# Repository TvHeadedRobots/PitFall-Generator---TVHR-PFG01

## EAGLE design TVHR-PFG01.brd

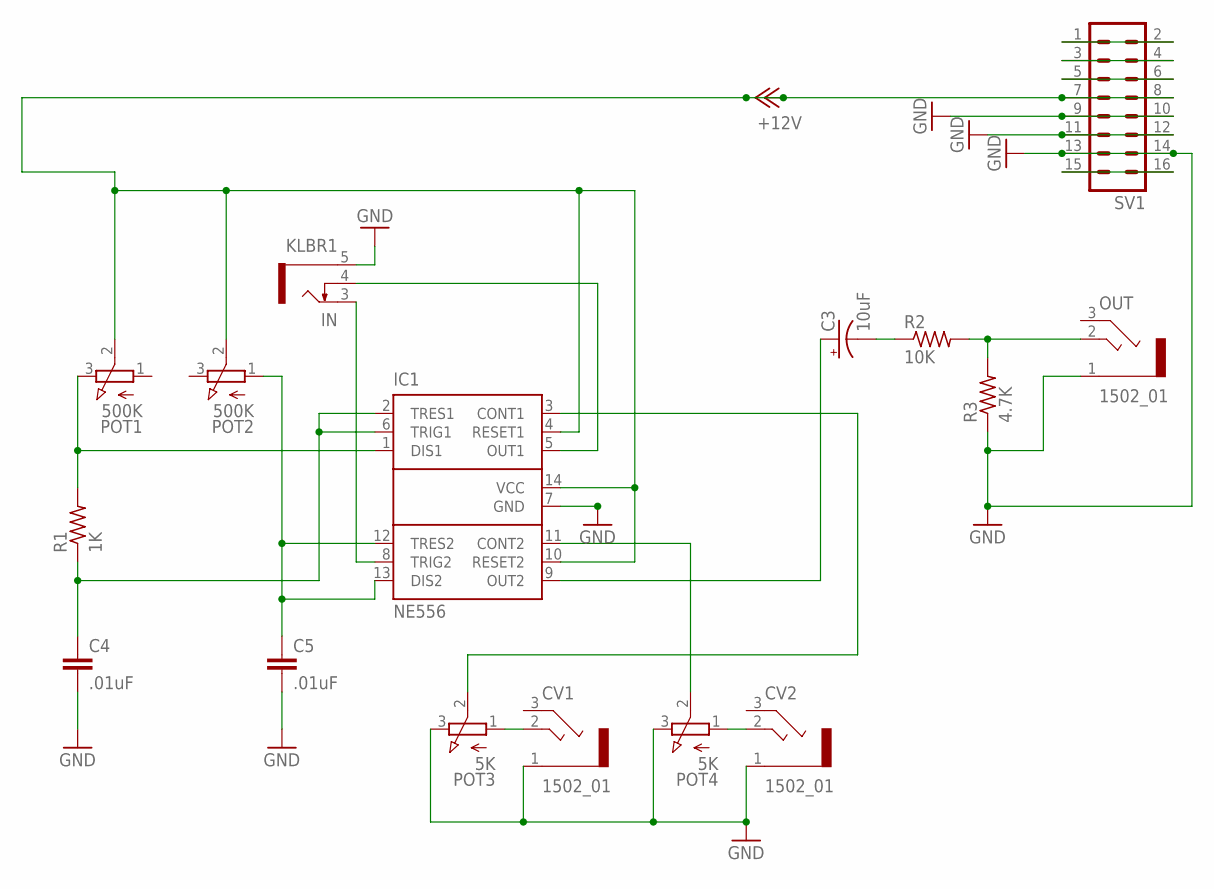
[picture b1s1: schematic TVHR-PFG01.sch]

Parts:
C3: 10uF; E2,5-5
C4, C5: .01uF; C2.5-3
CV1, CV2: 1502_01
IC1: NE556; DIL14
IN: KLBR1
OUT: 1502_01
POT1, POT2: 500K; 3RP/1610N
POT3, POT4: 5K; 3RP/1610N
R1: 1K; 0204/7
R2: 10K; 0204/7
R3: 4.7K; 0204/7
SV1: MA08-2

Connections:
+12V: IC1.4 (RESET1), IC1.10 (RESET2), IC1.14 (VCC), POT1.2 (S), POT2.2 (S), SV1.7, SV1.8
GND: C4.2, C5.2, CV1.1, CV2.1, IC1.7 (GND), IN.5, OUT.1, POT3.3 (E), POT4.3 (E), R3.1, SV1.9, SV1.10, SV1.11, SV1.12, SV1.13, SV1.14
unnamed: SV1.1, SV1.2
unnamed: IC1.1 (DIS1), POT1.3 (E), R1.2
unnamed: C4.1, IC1.2 (TRES1), IC1.6 (TRIG1), R1.1
unnamed: C5.1, IC1.12 (TRES2), IC1.13 (DIS2), POT2.1 (A)
unnamed: C3.-, R2.1
unnamed: IC1.5 (OUT1), IN.4
unnamed: C3.+, IC1.9 (OUT2)
unnamed: OUT.2 (3), R2.2, R3.2
unnamed: IC1.3 (CONT1), POT3.2 (S)
unnamed: IC1.11 (CONT2), POT4.2 (S)
unnamed: SV1.3, SV1.4
unnamed: SV1.5, SV1.6
unnamed: CV2.2 (3), POT4.1 (A)
unnamed: CV1.2 (3), POT3.1 (A)
unnamed: SV1.15, SV1.16
unnamed: IC1.8 (TRIG2), IN.3

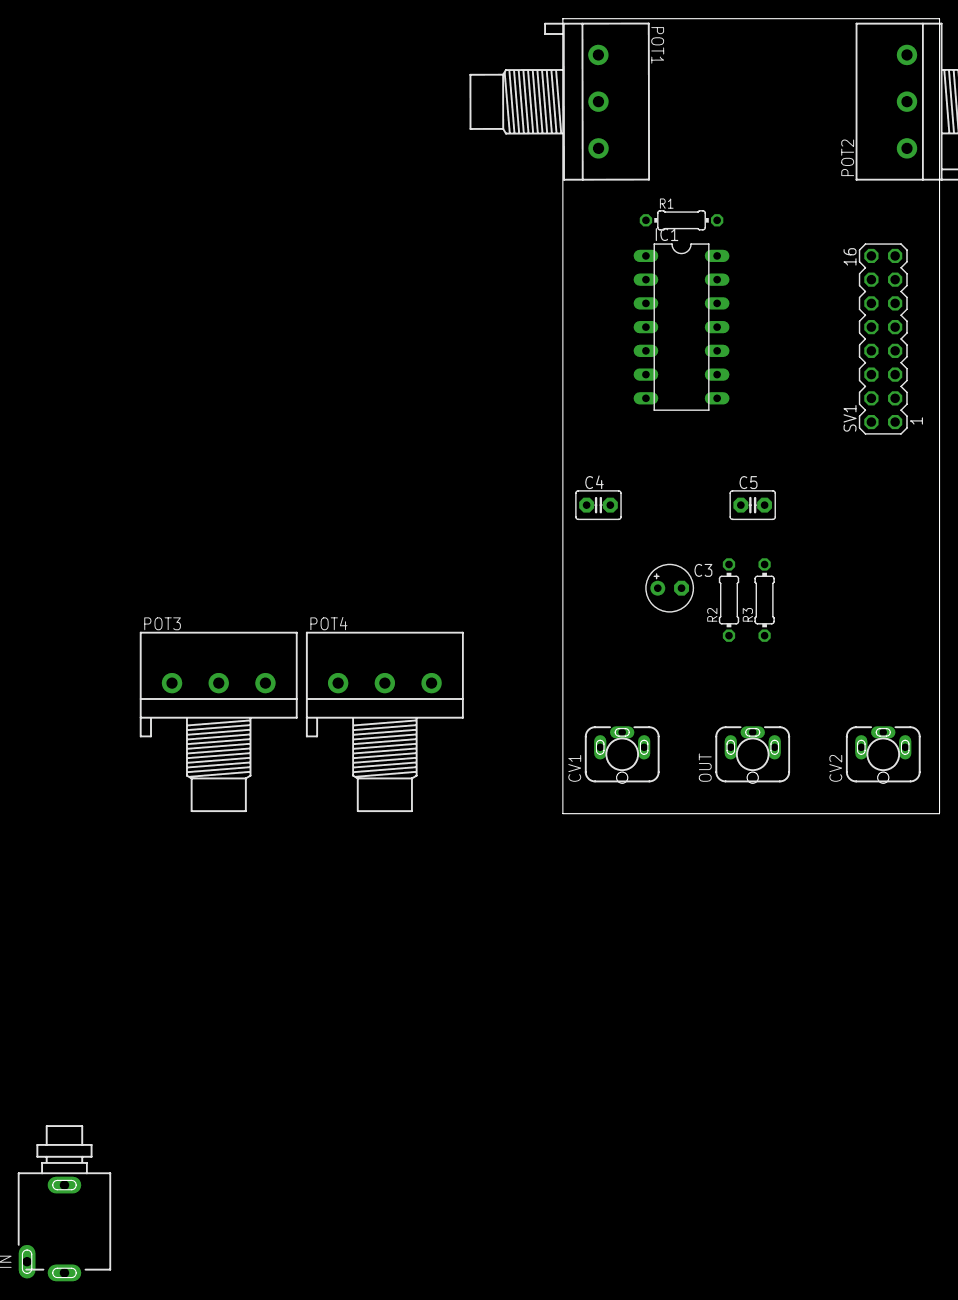
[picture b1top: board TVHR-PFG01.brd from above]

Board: 2 copper layers, 40.3 x 85.1 mm, 16 parts (0 on the bottom side), 18 nets.

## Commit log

2011-12-20 Adding the TVHR-PFG01 to my Git Repo
2012-05-29 Many changes across the entire project
